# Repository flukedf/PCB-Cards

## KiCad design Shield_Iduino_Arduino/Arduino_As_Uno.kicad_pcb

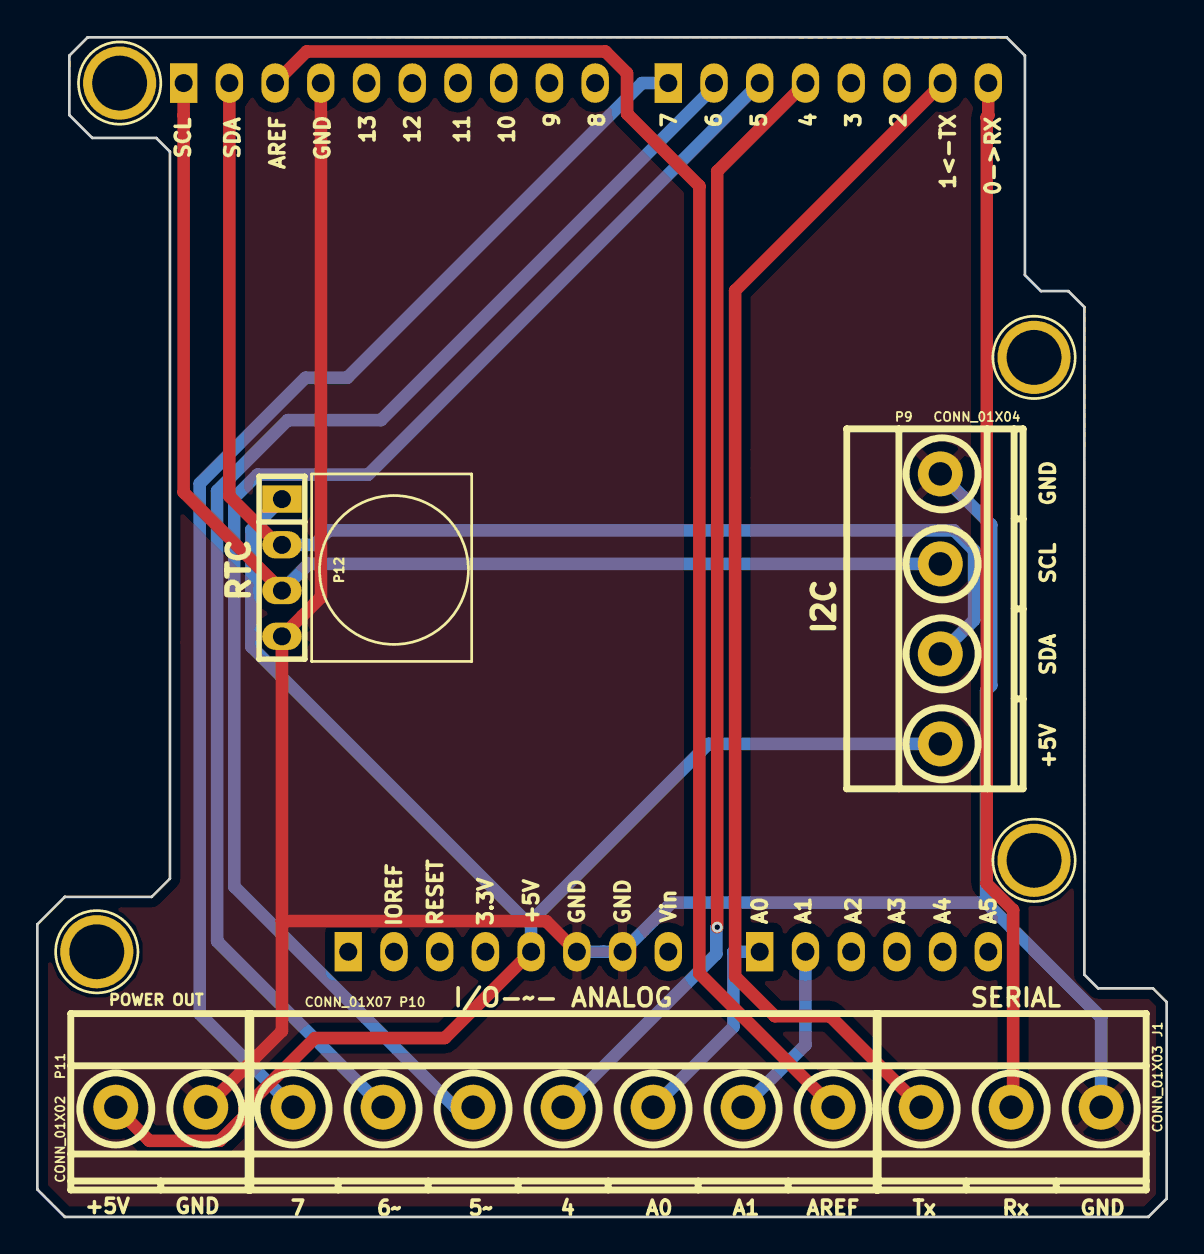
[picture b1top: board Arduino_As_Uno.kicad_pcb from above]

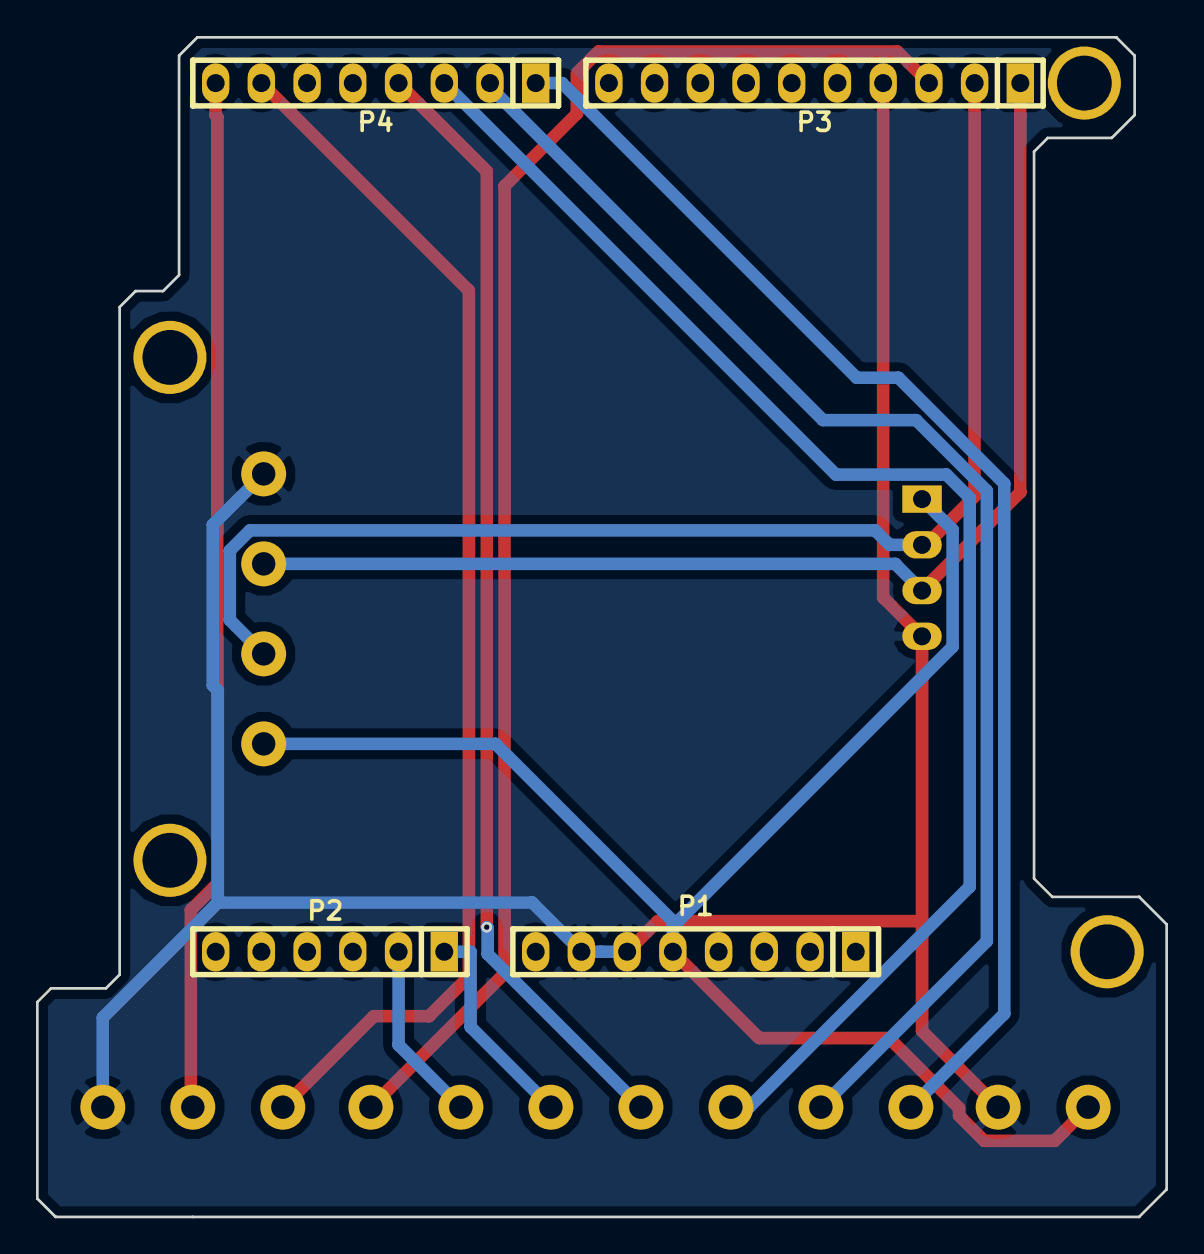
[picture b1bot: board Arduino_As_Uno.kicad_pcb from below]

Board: 2 copper layers, 62.7 x 65.5 mm, 13 parts (4 on the bottom side), 13 nets.

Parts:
J1: CONN_01X03; mkds_1,5-3
P1: Power; pin_strip_8
P2: Analog; pin_strip_6
P3: Digital; pin_strip_10
P4: Digital; pin_strip_8
P5, P6, P7, P8: CONN_01X01; Arduino_1pin
P9: CONN_01X04; mkds_1,5-4
P10: CONN_01X07; mkds_1,5-7
P11: CONN_01X02; mkds_1,5-2
P12: CONN_01X04; pin_socket_4

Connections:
+5V: P1.5, P9.1, P11.1, P12.1
/0(Rx): J1.2, P4.8
/1(Tx): J1.1, P4.7
/4: P4.4, P10.4
/5(**): P4.3, P10.3
/6(**): P4.2, P10.2
/7: P4.1, P10.1
/(SCL): P3.1, P9.3, P12.3
/(SDA): P3.2, P9.2, P12.2
/A0: P2.1, P10.5
/A1: P2.2, P10.6
/AREF: P3.3, P10.7
GND: J1.3, P1.6, P1.7, P3.4, P9.4, P11.2, P12.4

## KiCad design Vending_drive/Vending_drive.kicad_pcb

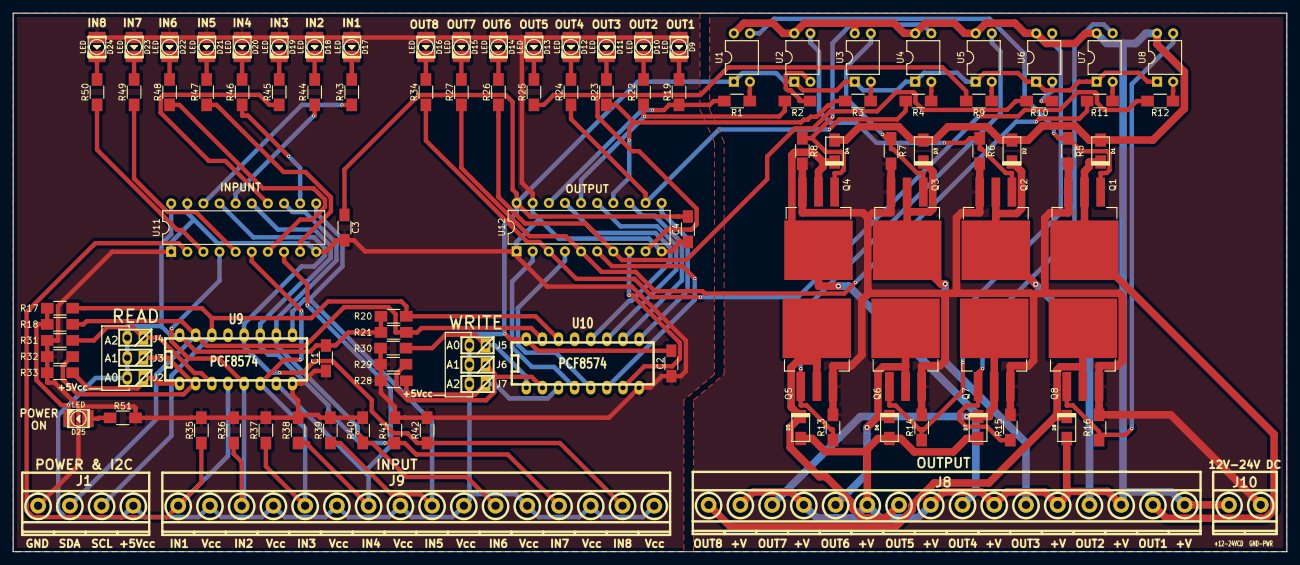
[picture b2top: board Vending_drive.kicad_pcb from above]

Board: 2 copper layers, 200.7 x 84.8 mm, 110 parts (0 on the bottom side), 85 nets.

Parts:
C1, C2, C3, C4: 100nF; C_1206_HandSoldering
D1, D2, D3, D4, D5, D6, D7, D8: D; do214ac
D9, D10, D11, D12, D13, D14, D15, D16, D17, D18, D19, D20, D21, D22, D23, D24, D25: LED; Led_PLCC2_3528
J1: POWER & I2C; mkds_1,5-4
J2, J5: A0; pin_strip_2
J3, J6: A1; pin_strip_2
J4, J7: A2; pin_strip_2
J8: OUTPUT; mkds_1,5-16
J9: INPUT; mkds_1,5-16
J10: 12V-24V DC; mkds_1,5-2
Q1, Q2, Q3, Q4, Q5, Q6, Q7, Q8: IRF540N; TO-263-3Lead
R1, R2, R3, R4, R9, R10, R11, R12: 470; R_1206_HandSoldering
R5, R6, R7, R8, R13, R14, R15, R16, R17, R18, R20, R21: 10K; R_1206_HandSoldering
R19, R22, R23, R24, R25, R26, R27, R34, R43, R44, R45, R46, R47, R48, R49, R50, R51: 330; R_1206_HandSoldering
R28, R29, R30, R31, R32, R33, R35, R36, R37, R38, R39, R40, R41, R42: 1K; R_1206_HandSoldering
U1, U2, U3, U4, U5, U6, U7, U8: PC817; DIP-4_W7.62mm
U9, U10: PCF8574; dil_16-300
U11, U12: 74LS244; DIP-20_W7.62mm

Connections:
+5Vcc: C1.2, C2.2, C3.1, C4.1, D25.2, J1.4, J2.2, J3.2, J4.2, J5.2, J6.2, J7.2, J9.2, J9.4, J9.6, J9.8, J9.10, J9.12, J9.14, J9.16, R17.1, R18.1, R20.1, R21.1, U1.1, U2.1, U3.1, U4.1, U5.1, U6.1, U7.1, U8.1, U9.16, U10.16, U11.20, U12.20
+24V: D1.1, D2.1, D3.1, D4.1, D5.1, D6.1, D7.1, D8.1, J8.2, J8.4, J8.6, J8.8, J8.10, J8.12, J8.14, J8.16, J10.1, U1.4, U2.4, U3.4, U4.4, U5.4, U6.4, U7.4, U8.4
GND: C1.1, C2.1, C3.2, C4.2, D9.1, D10.1, D11.1, D12.1, D13.1, D14.1, D15.1, D16.1, D17.1, D18.1, D19.1, D20.1, D21.1, D22.1, D23.1, D24.1, J1.1, R28.2, R29.2, R30.2, R31.2, R32.2, R33.2, R35.2, R36.2, R37.2, R38.2, R39.2, R40.2, R41.2, R42.2, R51.2, U9.8, U10.8, U11.1, U11.10, U11.19, U12.1, U12.10, U12.19
GNDPWR: J10.2, Q1.3, Q2.3, Q3.3, Q4.3, Q5.3, Q6.3, Q7.3, Q8.3, R5.2, R6.2, R7.2, R8.2, R13.2, R14.2, R15.2, R16.2
IN01: J9.1, R35.1, U9.4, U11.2
IN02: J9.3, R36.1, U9.5, U11.4
IN03: J9.5, R37.1, U9.6, U11.6
IN04: J9.7, R38.1, U9.7, U11.8
IN05: J9.9, R39.1, U9.9, U11.11
IN06: J9.11, R40.1, U9.10, U11.13
IN07: J9.13, R41.1, U9.11, U11.15
IN08: J9.15, R42.1, U9.12, U11.17
MOTOR_01-: D1.2, J8.15, Q1.2
MOTOR_02-: D2.2, J8.13, Q2.2
MOTOR_03-: D3.2, J8.11, Q3.2
MOTOR_04-: D4.2, J8.9, Q4.2
MOTOR_05-: D5.2, J8.7, Q5.2
MOTOR_06-: D6.2, J8.5, Q6.2
MOTOR_07-: D7.2, J8.3, Q7.2
MOTOR_08-: D8.2, J8.1, Q8.2
unnamed: D9.2, R19.2
unnamed: D10.2, R22.2
unnamed: D11.2, R23.2
unnamed: D12.2, R24.2
unnamed: D13.2, R25.2
unnamed: D14.2, R26.2
unnamed: D15.2, R27.2
unnamed: D16.2, R34.2
unnamed: D17.2, R43.2
unnamed: D18.2, R44.2
unnamed: D19.2, R45.2
unnamed: D20.2, R46.2
unnamed: D21.2, R47.2
unnamed: D22.2, R48.2
unnamed: D23.2, R49.2
unnamed: D24.2, R50.2
unnamed: D25.1, R51.1
unnamed: J2.1, R33.1, U9.1
unnamed: J3.1, R32.1, U9.2
unnamed: J4.1, R31.1, U9.3
unnamed: J5.1, R30.1, U10.1
unnamed: J6.1, R29.1, U10.2
unnamed: J7.1, R28.1, U10.3
unnamed: Q1.1, R5.1, U1.3
unnamed: Q2.1, R6.1, U2.3
unnamed: Q3.1, R7.1, U3.3
unnamed: Q4.1, R8.1, U4.3
unnamed: Q5.1, R13.1, U5.3
unnamed: Q6.1, R14.1, U6.3
unnamed: Q7.1, R15.1, U7.3
unnamed: Q8.1, R16.1, U8.3
unnamed: R1.1, U1.2
unnamed: R2.1, U2.2
unnamed: R3.1, U3.2
unnamed: R4.1, U4.2
unnamed: R9.1, U5.2
unnamed: R10.1, U6.2
unnamed: R11.1, U7.2
unnamed: R12.1, U8.2
Q1: R1.2, R19.1, U12.18
Q2: R2.2, R22.1, U12.16
Q3: R3.2, R23.1, U12.14
Q4: R4.2, R24.1, U12.12
Q5: R9.2, R25.1, U12.9
Q6: R10.2, R26.1, U12.7
Q7: R11.2, R27.1, U12.5
Q8: R12.2, R34.1, U12.3
S1: R43.1, U11.18
S2: R44.1, U11.16
S3: R45.1, U11.14
S4: R46.1, U11.12
S5: R47.1, U11.9
S6: R48.1, U11.7
S7: R49.1, U11.5
S8: R50.1, U11.3
SCL: J1.3, R17.2, R20.2, U9.14, U10.14
SDA: J1.2, R18.2, R21.2, U9.15, U10.15
SIGNAL_01: U10.4, U12.2
SIGNAL_02: U10.5, U12.4
SIGNAL_03: U10.6, U12.6
SIGNAL_04: U10.7, U12.8
SIGNAL_05: U10.9, U12.11
SIGNAL_06: U10.10, U12.13
SIGNAL_07: U10.11, U12.15
SIGNAL_08: U10.12, U12.17

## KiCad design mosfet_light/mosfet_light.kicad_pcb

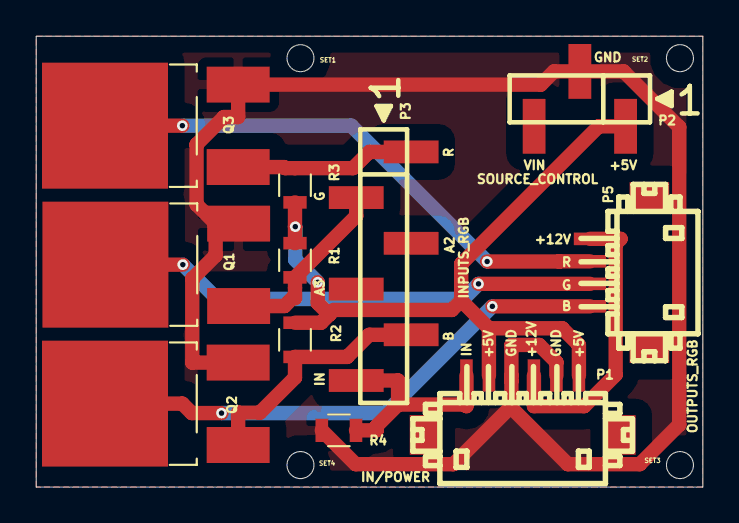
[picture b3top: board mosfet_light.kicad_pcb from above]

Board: 2 copper layers, 37.0 x 25.0 mm, 15 parts (0 on the bottom side), 10 nets.

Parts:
P1: IN/POWER; df13a-6p-125h
P2: SOURCE_CONTROL; bb02-hy03a
P3: INPUTS_RGB; bb02-hy06a
P5: OUTPUTS_RGB; df13a-4p-125h
Q1: GREEN; TO-252-2Lead
Q2: BLUE; TO-252-2Lead
Q3: RED; TO-252-2Lead
R1, R2, R3: 10K; R_0805
R4: 1K; R_0805
SET1, SET2, SET3, SET4: hole_001.5

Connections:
+5V: P1.1, P1.5, P2.1, R1.1, R2.1, R3.1
+12V: P1.3, P5.1
GND: P1.2, P1.4, P2.2, Q1.3, Q2.3, Q3.3, R4.2
unnamed: P1.6, P3.6, R4.1
unnamed: P3.1, Q3.1, R3.2
unnamed: P3.2, Q1.1, R1.2
unnamed: P3.5, Q2.1, R2.2
unnamed: P5.2, Q3.2
unnamed: P5.3, Q1.2
unnamed: P5.4, Q2.2

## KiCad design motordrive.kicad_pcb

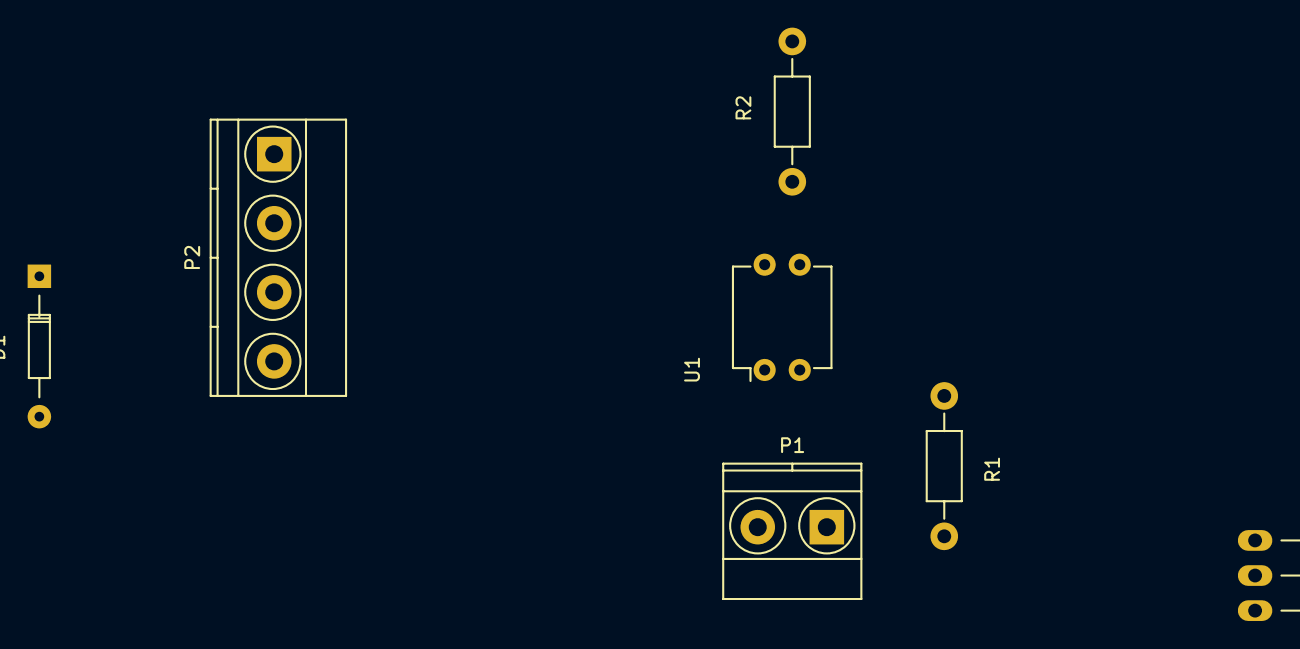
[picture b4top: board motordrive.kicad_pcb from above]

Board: 2 copper layers, 7 parts (0 on the bottom side), 7 nets, no tracks yet.

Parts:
D1: D; Diode_DO-35_SOD27_Horizontal_RM10
P1: CONN_01X02; TerminalBlock_Pheonix_MKDS1.5-2pol
P2: CONN_01X04; TerminalBlock_Pheonix_MKDS1.5-4pol
Q1: IRF540N; TO-220_Neutral123_Horizontal
R1: 470; Resistor_Horizontal_RM10mm
R2: 1K; Resistor_Horizontal_RM10mm
U1: PC817; DIP-4_W7.62mm

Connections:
GND: P2.2, Q1.3, R2.2
GND_CTRL: P1.1, R1.2
MOTOR+: D1.1, P2.1, P2.3, U1.4
MOTOR-: D1.2, P2.4, Q1.2
unnamed: Q1.1, R2.1, U1.3
unnamed: R1.1, U1.2
SIGNAL: P1.2, U1.1
